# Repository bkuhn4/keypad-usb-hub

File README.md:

# keypad-usb-hub

## Getting started

To make it easy for you to get started with GitLab, here's a list of recommended next steps.

Already a pro? Just edit this README.md and make it your own. Want to make it easy? [Use the template at the bottom](#editing-this-readme)!

## Add your files

* \[ ] [Create](https://docs.gitlab.com/ee/user/project/repository/web_editor.html#create-a-file) or [upload](https://docs.gitlab.com/ee/user/project/repository/web_editor.html#upload-a-file) files
* \[ ] [Add files using the command line](https://docs.gitlab.com/ee/gitlab-basics/add-file.html#add-a-file-using-the-command-line) or push an existing Git repository with the following command:

```
cd existing\_repo
git remote add origin https://git.ece.iastate.edu/etg\_dev/micro\_sd\_card.git
git branch -M main
git push -uf origin main
```

## Integrate with your tools

* \[ ] [Set up project integrations](https://git.ece.iastate.edu/etg_dev/micro_sd_card/-/settings/integrations)

## Collaborate with your team

* \[ ] [Invite team members and collaborators](https://docs.gitlab.com/ee/user/project/members/)
* \[ ] [Create a new merge request](https://docs.gitlab.com/ee/user/project/merge_requests/creating_merge_requests.html)
* \[ ] [Automatically close issues from merge requests](https://docs.gitlab.com/ee/user/project/issues/managing_issues.html#closing-issues-automatically)
* \[ ] [Enable merge request approvals](https://docs.gitlab.com/ee/user/project/merge_requests/approvals/)
* \[ ] [Set auto-merge](https://docs.gitlab.com/ee/user/project/merge_requests/merge_when_pipeline_succeeds.html)

## Test and Deploy

Use the built-in continuous integration in GitLab.

* \[ ] [Get started with GitLab CI/CD](https://docs.gitlab.com/ee/ci/quick_start/index.html)
* \[ ] [Analyze your code for known vulnerabilities with Static Application Security Testing (SAST)](https://docs.gitlab.com/ee/user/application_security/sast/)
* \[ ] [Deploy to Kubernetes, Amazon EC2, or Amazon ECS using Auto Deploy](https://docs.gitlab.com/ee/topics/autodevops/requirements.html)
* \[ ] [Use pull-based deployments for improved Kubernetes management](https://docs.gitlab.com/ee/user/clusters/agent/)
* \[ ] [Set up protected environments](https://docs.gitlab.com/ee/ci/environments/protected_environments.html)

---

# Editing this README

When you're ready to make this README your own, just edit this file and use the handy template below (or feel free to structure it however you want - this is just a starting point!). Thanks to [makeareadme.com](https://www.makeareadme.com/) for this template.

## Suggestions for a good README

Every project is different, so consider which of these sections apply to yours. The sections used in the template are suggestions for most open source projects. Also keep in mind that while a README can be too long and detailed, too long is better than too short. If you think your README is too long, consider utilizing another form of documentation rather than cutting out information.

## Name

Choose a self-explaining name for your project.

## Description

Let people know what your project can do specifically. Provide context and add a link to any reference visitors might be unfamiliar with. A list of Features or a Background subsection can also be added here. If there are alternatives to your project, this is a good place to list differentiating factors.

## Badges

On some READMEs, you may see small images that convey metadata, such as whether or not all the tests are passing for the project. You can use Shields to add some to your README. Many services also have instructions for adding a badge.

## Visuals

Depending on what you are making, it can be a good idea to include screenshots or even a video (you'll frequently see GIFs rather than actual videos). Tools like ttygif can help, but check out Asciinema for a more sophisticated method.

## Installation

Within a particular ecosystem, there may be a common way of installing things, such as using Yarn, NuGet, or Homebrew. However, consider the possibility that whoever is reading your README is a novice and would like more guidance. Listing specific steps helps remove ambiguity and gets people to using your project as quickly as possible. If it only runs in a specific context like a particular programming language version or operating system or has dependencies that have to be installed manually, also add a Requirements subsection.

## Usage

Use examples liberally, and show the expected output if you can. It's helpful to have inline the smallest example of usage that you can demonstrate, while providing links to more sophisticated examples if they are too long to reasonably include in the README.

## Support

Tell people where they can go to for help. It can be any combination of an issue tracker, a chat room, an email address, etc.

## Roadmap

If you have ideas for releases in the future, it is a good idea to list them in the README.

## Contributing

State if you are open to contributions and what your requirements are for accepting them.

For people who want to make changes to your project, it's helpful to have some documentation on how to get started. Perhaps there is a script that they should run or some environment variables that they need to set. Make these steps explicit. These instructions could also be useful to your future self.

You can also document commands to lint the code or run tests. These steps help to ensure high code quality and reduce the likelihood that the changes inadvertently break something. Having instructions for running tests is especially helpful if it requires external setup, such as starting a Selenium server for testing in a browser.

## Authors and acknowledgment

Show your appreciation to those who have contributed to the project.

## License

For open source projects, say how it is licensed.

## Project status

If you have run out of energy or time for your project, put a note at the top of the README saying that development has slowed down or stopped completely. Someone may choose to fork your project or volunteer to step in as a maintainer or owner, allowing your project to keep going. You can also make an explicit request for maintainers.

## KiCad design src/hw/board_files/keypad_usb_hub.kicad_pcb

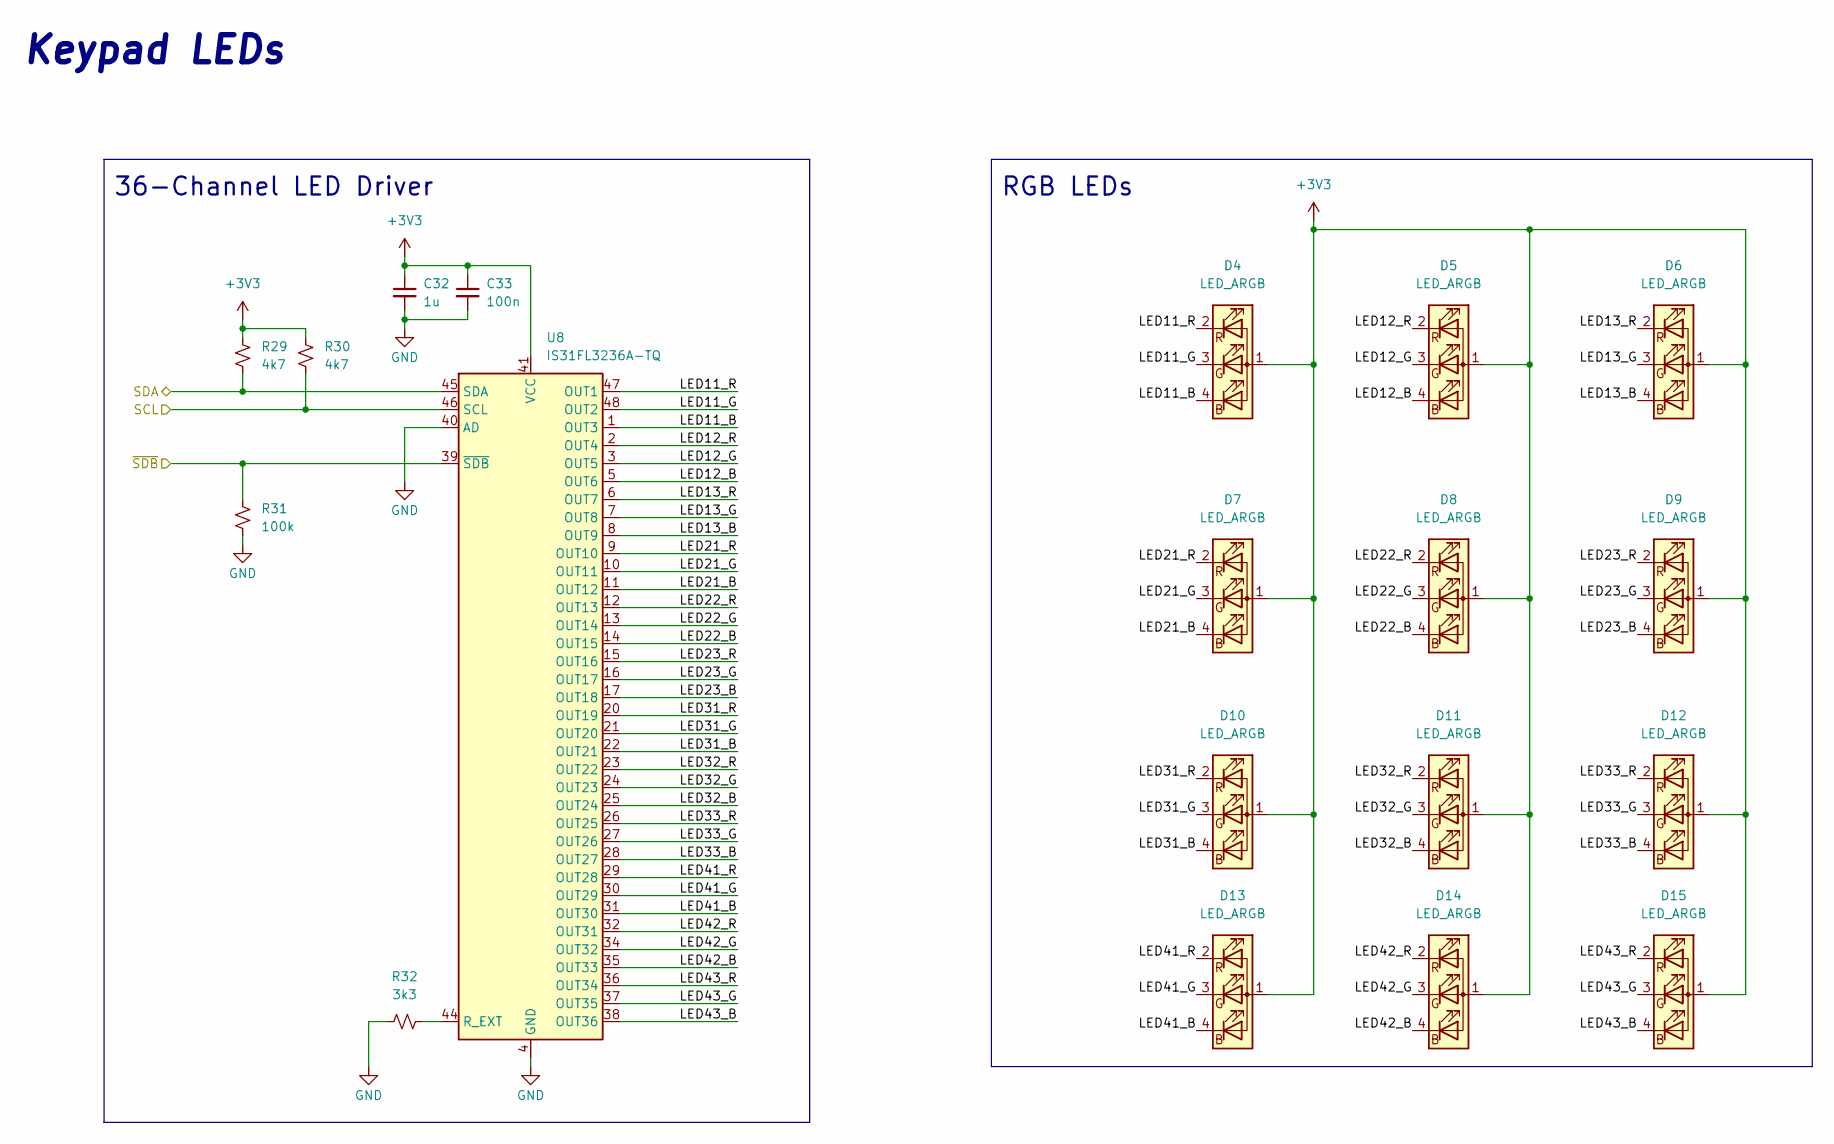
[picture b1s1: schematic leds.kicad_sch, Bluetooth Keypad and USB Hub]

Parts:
C32: 1u; C_0603_1608Metric_Pad1.08x0.95mm_HandSolder
C33: 100n; C_0603_1608Metric_Pad1.08x0.95mm_HandSolder
D4, D5, D6, D7, D8, D9, D10, D11, D12, D13, D14, D15: LED_ARGB; RGB_LED_6028_Reverse_Mount
R29, R30: 4k7; R_0603_1608Metric_Pad0.98x0.95mm_HandSolder
R31: 100k; R_0805_2012Metric_Pad1.20x1.40mm_HandSolder
R32: 3k3; R_0603_1608Metric_Pad0.98x0.95mm_HandSolder
U8: IS31FL3236A-TQ; TQFP-48-1EP_7x7mm_P0.5mm_EP4.11x4.11mm

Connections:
+3V3: C32.1, C33.1, D4.1 (A), D5.1 (A), D6.1 (A), D7.1 (A), D8.1 (A), D9.1 (A), D10.1 (A), D11.1 (A), D12.1 (A), D13.1 (A), D14.1 (A), D15.1 (A), R29.1, R30.1, U8.41 (VCC); also elsewhere on the board
/LEDs/LED11_B: D4.4 (BK), U8.1 (OUT3)
/LEDs/LED11_G: D4.3 (GK), U8.48 (OUT2)
/LEDs/LED11_R: D4.2 (RK), U8.47 (OUT1)
/LEDs/LED12_B: D5.4 (BK), U8.5 (OUT6)
/LEDs/LED12_G: D5.3 (GK), U8.3 (OUT5)
/LEDs/LED12_R: D5.2 (RK), U8.2 (OUT4)
/LEDs/LED13_B: D6.4 (BK), U8.8 (OUT9)
/LEDs/LED13_G: D6.3 (GK), U8.7 (OUT8)
/LEDs/LED13_R: D6.2 (RK), U8.6 (OUT7)
/LEDs/LED21_B: D7.4 (BK), U8.11 (OUT12)
/LEDs/LED21_G: D7.3 (GK), U8.10 (OUT11)
/LEDs/LED21_R: D7.2 (RK), U8.9 (OUT10)
/LEDs/LED22_B: D8.4 (BK), U8.14 (OUT15)
/LEDs/LED22_G: D8.3 (GK), U8.13 (OUT14)
/LEDs/LED22_R: D8.2 (RK), U8.12 (OUT13)
/LEDs/LED23_B: D9.4 (BK), U8.17 (OUT18)
/LEDs/LED23_G: D9.3 (GK), U8.16 (OUT17)
/LEDs/LED23_R: D9.2 (RK), U8.15 (OUT16)
/LEDs/LED31_B: D10.4 (BK), U8.22 (OUT21)
/LEDs/LED31_G: D10.3 (GK), U8.21 (OUT20)
/LEDs/LED31_R: D10.2 (RK), U8.20 (OUT19)
/LEDs/LED32_B: D11.4 (BK), U8.25 (OUT24)
/LEDs/LED32_G: D11.3 (GK), U8.24 (OUT23)
/LEDs/LED32_R: D11.2 (RK), U8.23 (OUT22)
/LEDs/LED33_B: D12.4 (BK), U8.28 (OUT27)
/LEDs/LED33_G: D12.3 (GK), U8.27 (OUT26)
/LEDs/LED33_R: D12.2 (RK), U8.26 (OUT25)
/LEDs/LED41_B: D13.4 (BK), U8.31 (OUT30)
/LEDs/LED41_G: D13.3 (GK), U8.30 (OUT29)
/LEDs/LED41_R: D13.2 (RK), U8.29 (OUT28)
/LEDs/LED42_B: D14.4 (BK), U8.35 (OUT33)
/LEDs/LED42_G: D14.3 (GK), U8.34 (OUT32)
/LEDs/LED42_R: D14.2 (RK), U8.32 (OUT31)
/LEDs/LED43_B: D15.4 (BK), U8.38 (OUT36)
/LEDs/LED43_G: D15.3 (GK), U8.37 (OUT35)
/LEDs/LED43_R: D15.2 (RK), U8.36 (OUT34)
/LEDs/SCL: R30.2, U8.46 (SCL); also elsewhere on the board
/LEDs/SDA: R29.2, U8.45 (SDA); also elsewhere on the board
/LEDs/~SDB: R31.1, U8.39 (~SDB); also elsewhere on the board
GND: C32.2, C33.2, R31.2, R32.2, U8.4 (GND), U8.18 (GND), U8.19 (GND), U8.33 (GND), U8.40 (AD), U8.42 (GND), U8.43 (GND), U8.49 (GND); also elsewhere on the board
unnamed: R32.1, U8.44 (R_EXT)

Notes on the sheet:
Keypad LEDs
RGB LEDs
36-Channel LED Driver

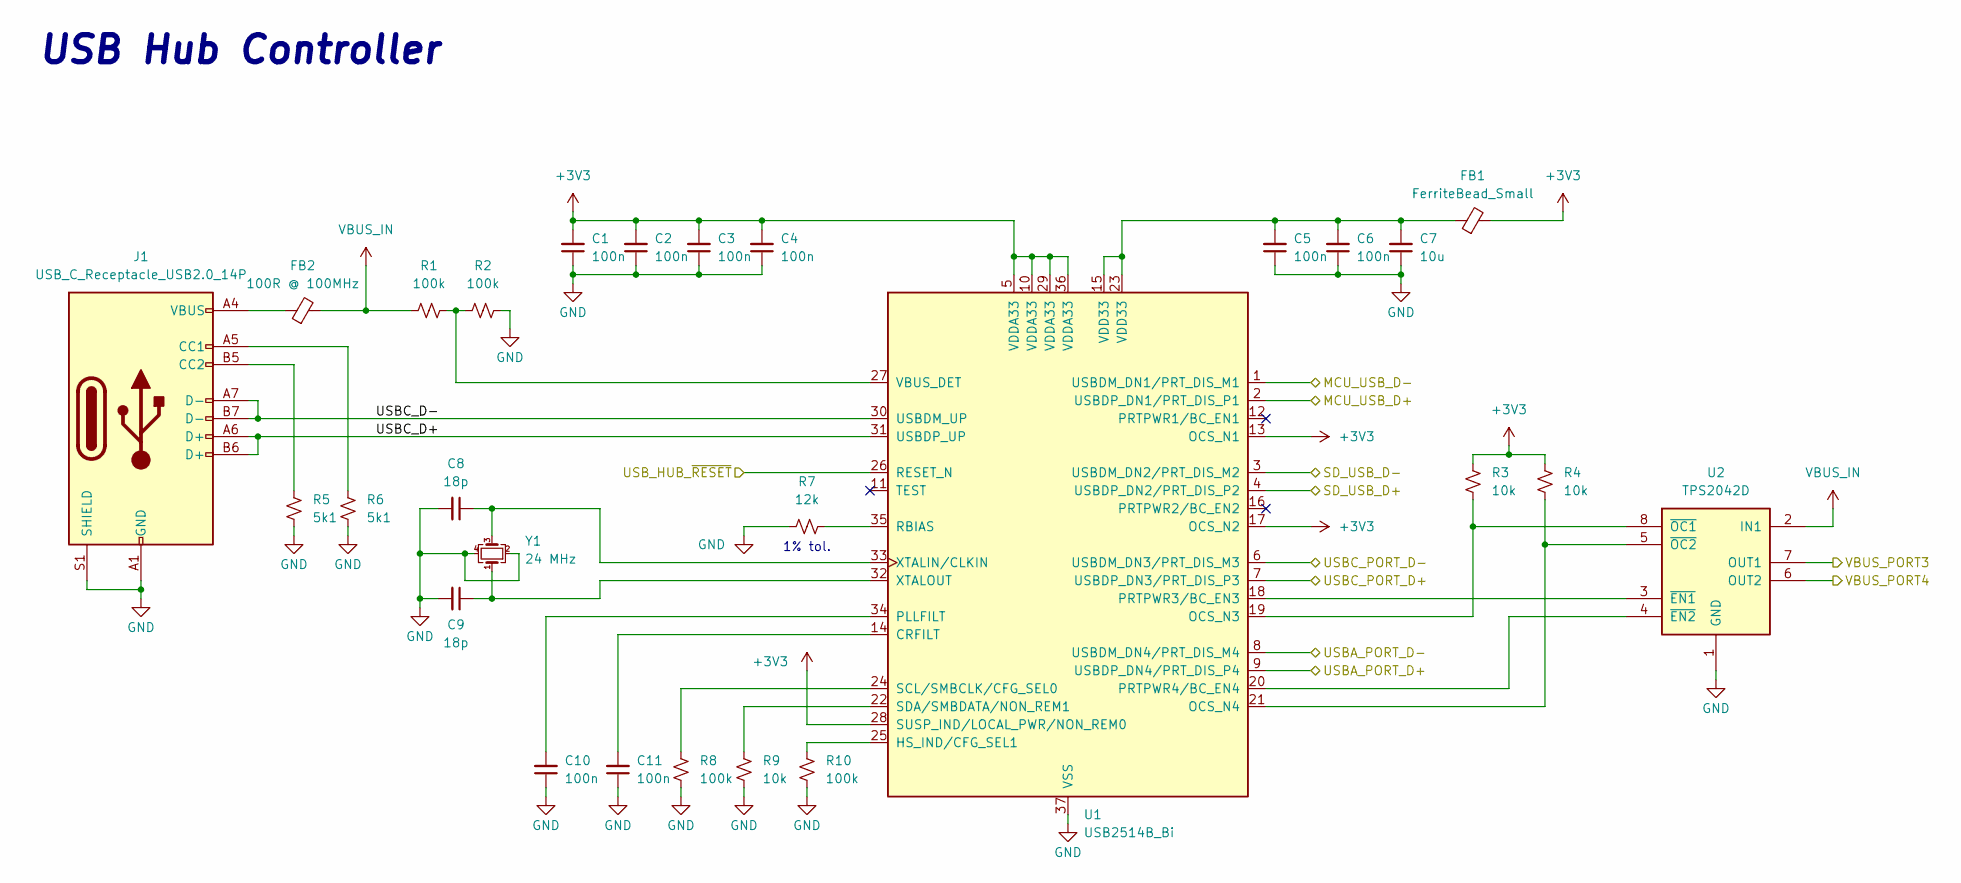
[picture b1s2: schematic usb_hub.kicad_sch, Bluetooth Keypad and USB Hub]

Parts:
C1, C2, C3, C4, C5, C6, C10, C11: 100n; C_0603_1608Metric_Pad1.08x0.95mm_HandSolder
C7: 10u; C_0805_2012Metric_Pad1.18x1.45mm_HandSolder
C8, C9: 18p; C_0603_1608Metric_Pad1.08x0.95mm_HandSolder
FB1: FerriteBead_Small; L_0603_1608Metric_Pad1.05x0.95mm_HandSolder
FB2: 100R @ 100MHz; L_0805_2012Metric_Pad1.15x1.40mm_HandSolder
J1: USB_C_Receptacle_USB2.0_14P; USB_C_Receptacle_GCT_USB4105-xx-A_16P_TopMnt_Horizontal
R1, R2, R8, R10: 100k; R_0805_2012Metric_Pad1.20x1.40mm_HandSolder
R3, R4, R9: 10k; R_0603_1608Metric_Pad0.98x0.95mm_HandSolder
R5, R6: 5k1; R_0603_1608Metric_Pad0.98x0.95mm_HandSolder
R7: 12k; R_0603_1608Metric_Pad0.98x0.95mm_HandSolder
U1: USB2514B_Bi; QFN-36-1EP_6x6mm_P0.5mm_EP3.7x3.7mm
U2: TPS2042D; SOIC-8_3.9x4.9mm_P1.27mm
Y1: 24 MHz; Crystal_SMD_Abracon_ABM8G-4Pin_3.2x2.5mm

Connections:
+3V3: C1.2, C2.2, C3.2, C4.2, FB1.2, R3.2, R4.2, U1.5 (VDDA33), U1.10 (VDDA33), U1.13 (OCS_N1), U1.17 (OCS_N2), U1.28 (SUSP_IND/LOCAL_PWR/NON_REM0), U1.29 (VDDA33), U1.36 (VDDA33); also elsewhere on the board
/Microcontroller and Power/MCU_USB_D+: U1.2 (USBDP_DN1/PRT_DIS_P1); also elsewhere on the board
/Microcontroller and Power/MCU_USB_D-: U1.1 (USBDM_DN1/PRT_DIS_M1); also elsewhere on the board
/Microcontroller and Power/USB_HUB_~RESET: U1.26 (RESET_N); also elsewhere on the board
/Receptacles/SD_USB_D+: U1.4 (USBDP_DN2/PRT_DIS_P2); also elsewhere on the board
/Receptacles/SD_USB_D-: U1.3 (USBDM_DN2/PRT_DIS_M2); also elsewhere on the board
/Receptacles/USBA_PORT_D+: U1.9 (USBDP_DN4/PRT_DIS_P4); also elsewhere on the board
/Receptacles/USBA_PORT_D-: U1.8 (USBDM_DN4/PRT_DIS_M4); also elsewhere on the board
/Receptacles/USBC_PORT_D+: U1.7 (USBDP_DN3/PRT_DIS_P3); also elsewhere on the board
/Receptacles/USBC_PORT_D-: U1.6 (USBDM_DN3/PRT_DIS_M3); also elsewhere on the board
/Receptacles/VBUS_PORT4: U2.6 (OUT2); also elsewhere on the board
/USB Hub Controller/USBC_D+: J1.A6 (D+), J1.B6 (D+), U1.31 (USBDP_UP)
/USB Hub Controller/USBC_D-: J1.A7 (D-), J1.B7 (D-), U1.30 (USBDM_UP)
GND: C1.1, C2.1, C3.1, C4.1, C5.1, C6.1, C7.1, C8.2, C9.2, C10.1, C11.1, J1.A1 (GND), J1.A12 (GND), J1.B1 (GND), J1.B12 (GND), J1.S1 (SHIELD), R2.1, R5.1, R6.1, R7.1, R8.1, R9.1, R10.1, U1.37 (VSS), U2.1 (GND), Y1.2, Y1.4; also elsewhere on the board
unnamed: C5.2, C6.2, C7.2, FB1.1, U1.15 (VDD33), U1.23 (VDD33)
unnamed: FB2.1, J1.A4 (VBUS), J1.A9 (VBUS), J1.B4 (VBUS), J1.B9 (VBUS)
unnamed: J1.A5 (CC1), R6.2
unnamed: J1.B5 (CC2), R5.2
unnamed: C11.2, U1.14 (CRFILT)
unnamed: R10.2, U1.25 (HS_IND/CFG_SEL1)
unnamed: R3.1, U1.19 (OCS_N3), U2.8 (~OC1)
unnamed: R4.1, U1.21 (OCS_N4), U2.5 (~OC2)
unnamed: C10.2, U1.34 (PLLFILT)
unnamed: U1.18 (PRTPWR3/BC_EN3), U2.3 (~EN1)
unnamed: U1.20 (PRTPWR4/BC_EN4), U2.4 (~EN2)
unnamed: R7.2, U1.35 (RBIAS)
unnamed: R8.2, U1.24 (SCL/SMBCLK/CFG_SEL0)
unnamed: R9.2, U1.22 (SDA/SMBDATA/NON_REM1)
unnamed: R1.1, R2.2, U1.27 (VBUS_DET)
unnamed: C8.1, U1.33 (XTALIN/CLKIN), Y1.3
unnamed: C9.1, U1.32 (XTALOUT), Y1.1
VBUS_IN: FB2.2, R1.2, U2.2 (IN1); also elsewhere on the board
VBUS_PORT3: U2.7 (OUT1); also elsewhere on the board

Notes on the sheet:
USB Hub Controller
1% tol.

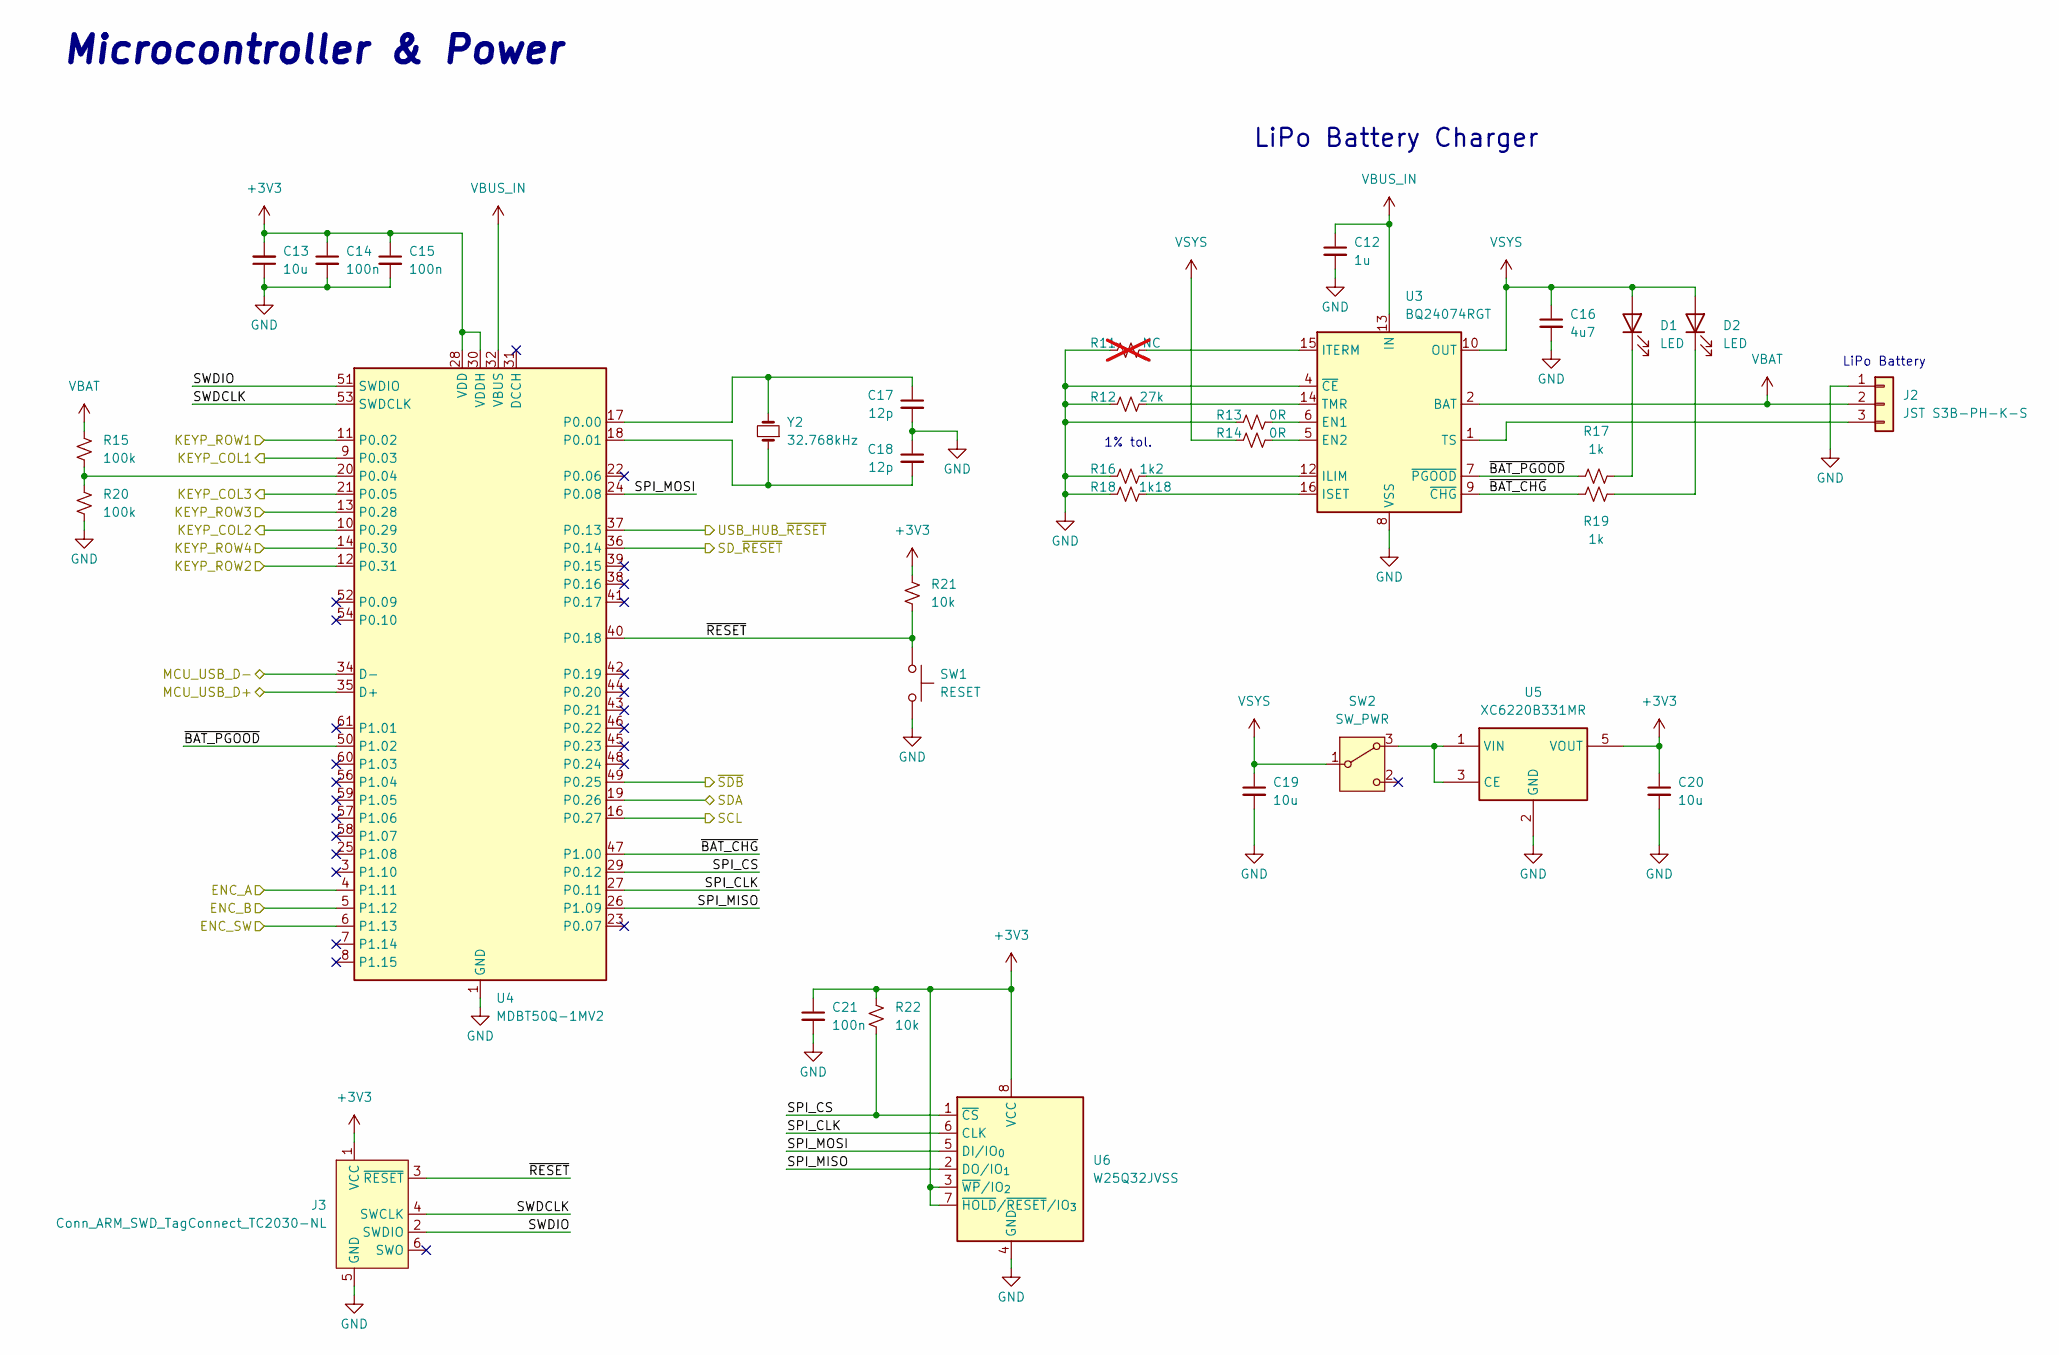
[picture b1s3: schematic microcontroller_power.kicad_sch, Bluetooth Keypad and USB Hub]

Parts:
C12: 1u; C_0603_1608Metric_Pad1.08x0.95mm_HandSolder
C13, C19, C20: 10u; C_0805_2012Metric_Pad1.18x1.45mm_HandSolder
C14, C15, C21: 100n; C_0603_1608Metric_Pad1.08x0.95mm_HandSolder
C16: 4u7; C_0805_2012Metric_Pad1.18x1.45mm_HandSolder
C17, C18: 12p; C_0603_1608Metric_Pad1.08x0.95mm_HandSolder
D1, D2: LED; LED_0603_1608Metric_Pad1.05x0.95mm_HandSolder
J2: JST S3B-PH-K-S; JST_PH_S3B-PH-K_1x03_P2.00mm_Horizontal
J3: Conn_ARM_SWD_TagConnect_TC2030-NL; Tag-Connect_TC2030-IDC-NL_2x03_P1.27mm_Vertical
R11: NC; R_0603_1608Metric_Pad0.98x0.95mm_HandSolder; not fitted
R12: 27k; R_0603_1608Metric_Pad0.98x0.95mm_HandSolder
R13, R14: 0R; R_0603_1608Metric_Pad0.98x0.95mm_HandSolder
R15, R20: 100k; R_0805_2012Metric_Pad1.20x1.40mm_HandSolder
R16: 1k2; R_0603_1608Metric_Pad0.98x0.95mm_HandSolder
R17, R19: 1k; R_0603_1608Metric_Pad0.98x0.95mm_HandSolder
R18: 1k18; R_0603_1608Metric_Pad0.98x0.95mm_HandSolder
R21, R22: 10k; R_0603_1608Metric_Pad0.98x0.95mm_HandSolder
SW1: RESET; SW_PUSH_6mm
SW2: SW_PWR; SW_Slide-03_Wuerth-WS-SLTV_10x2.5x6.4_P2.54mm
U3: BQ24074RGT; VQFN-16-1EP_3x3mm_P0.5mm_EP1.6x1.6mm
U4: MDBT50Q-1MV2; Raytac_MDBT50Q
U5: XC6220B331MR; SOT-23-5
U6: W25Q32JVSS; SOIC-8_5.3x5.3mm_P1.27mm
Y2: 32.768kHz; Crystal_SMD_3215-2Pin_3.2x1.5mm

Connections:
+3V3: C13.2, C14.1, C15.1, C20.1, C21.1, J3.1 (VCC), R21.2, R22.2, U4.28 (VDD), U4.30 (VDDH), U5.5 (VOUT), U6.3 (~WP/IO_{2}), U6.7 (~HOLD/~RESET/IO_{3}), U6.8 (VCC); also elsewhere on the board
/LEDs/SCL: U4.16 (P0.27); also elsewhere on the board
/LEDs/SDA: U4.19 (P0.26); also elsewhere on the board
/LEDs/~SDB: U4.49 (P0.25); also elsewhere on the board
/Microcontroller and Power/ENC_A: U4.4 (P1.11); also elsewhere on the board
/Microcontroller and Power/ENC_B: U4.5 (P1.12); also elsewhere on the board
/Microcontroller and Power/ENC_SW: U4.6 (P1.13); also elsewhere on the board
/Microcontroller and Power/KEYP_COL1: U4.9 (P0.03); also elsewhere on the board
/Microcontroller and Power/KEYP_COL2: U4.10 (P0.29); also elsewhere on the board
/Microcontroller and Power/KEYP_COL3: U4.21 (P0.05); also elsewhere on the board
/Microcontroller and Power/KEYP_ROW1: U4.11 (P0.02); also elsewhere on the board
/Microcontroller and Power/KEYP_ROW2: U4.12 (P0.31); also elsewhere on the board
/Microcontroller and Power/KEYP_ROW3: U4.13 (P0.28); also elsewhere on the board
/Microcontroller and Power/KEYP_ROW4: U4.14 (P0.30); also elsewhere on the board
/Microcontroller and Power/MCU_USB_D+: U4.35 (D+); also elsewhere on the board
/Microcontroller and Power/MCU_USB_D-: U4.34 (D-); also elsewhere on the board
/Microcontroller and Power/SD_~RESET: U4.36 (P0.14); also elsewhere on the board
/Microcontroller and Power/SPI_CLK: U4.27 (P0.11), U6.6 (CLK)
/Microcontroller and Power/SPI_CS: R22.1, U4.29 (P0.12), U6.1 (~CS)
/Microcontroller and Power/SPI_MISO: U4.26 (P1.09), U6.2 (DO/IO_{1})
/Microcontroller and Power/SPI_MOSI: U4.24 (P0.08), U6.5 (DI/IO_{0})
/Microcontroller and Power/SWDCLK: J3.4 (SWCLK), U4.53 (SWDCLK)
/Microcontroller and Power/SWDIO: J3.2 (SWDIO), U4.51 (SWDIO)
/Microcontroller and Power/USB_HUB_~RESET: U4.37 (P0.13); also elsewhere on the board
/Microcontroller and Power/~BAT_CHG: R19.1, U3.9 (~CHG), U4.47 (P1.00)
/Microcontroller and Power/~BAT_PGOOD: R17.1, U3.7 (~PGOOD), U4.50 (P1.02)
/Microcontroller and Power/~RESET: J3.3 (~RESET), R21.1, SW1.1, U4.40 (P0.18)
GND: C12.2, C13.1, C14.2, C15.2, C16.2, C17.2, C18.1, C19.2, C20.2, C21.2, J2.1, J3.5 (GND), R11.2, R12.2, R13.2, R16.2, R18.2, R20.2, SW1.2, U3.4 (~CE), U3.8 (VSS), U3.17 (VSS), U4.1 (GND), U4.2 (GND), U4.15 (GND), U4.33 (GND), U4.55 (GND), U5.2 (GND), U6.4 (GND); also elsewhere on the board
unnamed: D1.1 (K), R17.2
unnamed: D2.1 (K), R19.2
unnamed: J2.3, U3.1 (TS)
unnamed: SW2.3 (A), U5.1 (VIN), U5.3 (CE)
unnamed: R13.1, U3.6 (EN1)
unnamed: R14.1, U3.5 (EN2)
unnamed: R16.1, U3.12 (ILIM)
unnamed: R18.1, U3.16 (ISET)
unnamed: R11.1, U3.15 (ITERM)
unnamed: R12.1, U3.14 (TMR)
unnamed: C17.1, U4.17 (P0.00), Y2.2
unnamed: C18.2, U4.18 (P0.01), Y2.1
unnamed: R15.2, R20.1, U4.20 (P0.04)
VBAT: J2.2, R15.1, U3.2 (BAT), U3.3 (BAT)
VBUS_IN: C12.1, U3.13 (IN), U4.32 (VBUS); also elsewhere on the board
VSYS: C16.1, C19.1, D1.2 (A), D2.2 (A), R14.2, SW2.1 (B), U3.10 (OUT), U3.11 (OUT)

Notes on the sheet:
LiPo Battery
1% tol.
Microcontroller & Power
LiPo Battery Charger

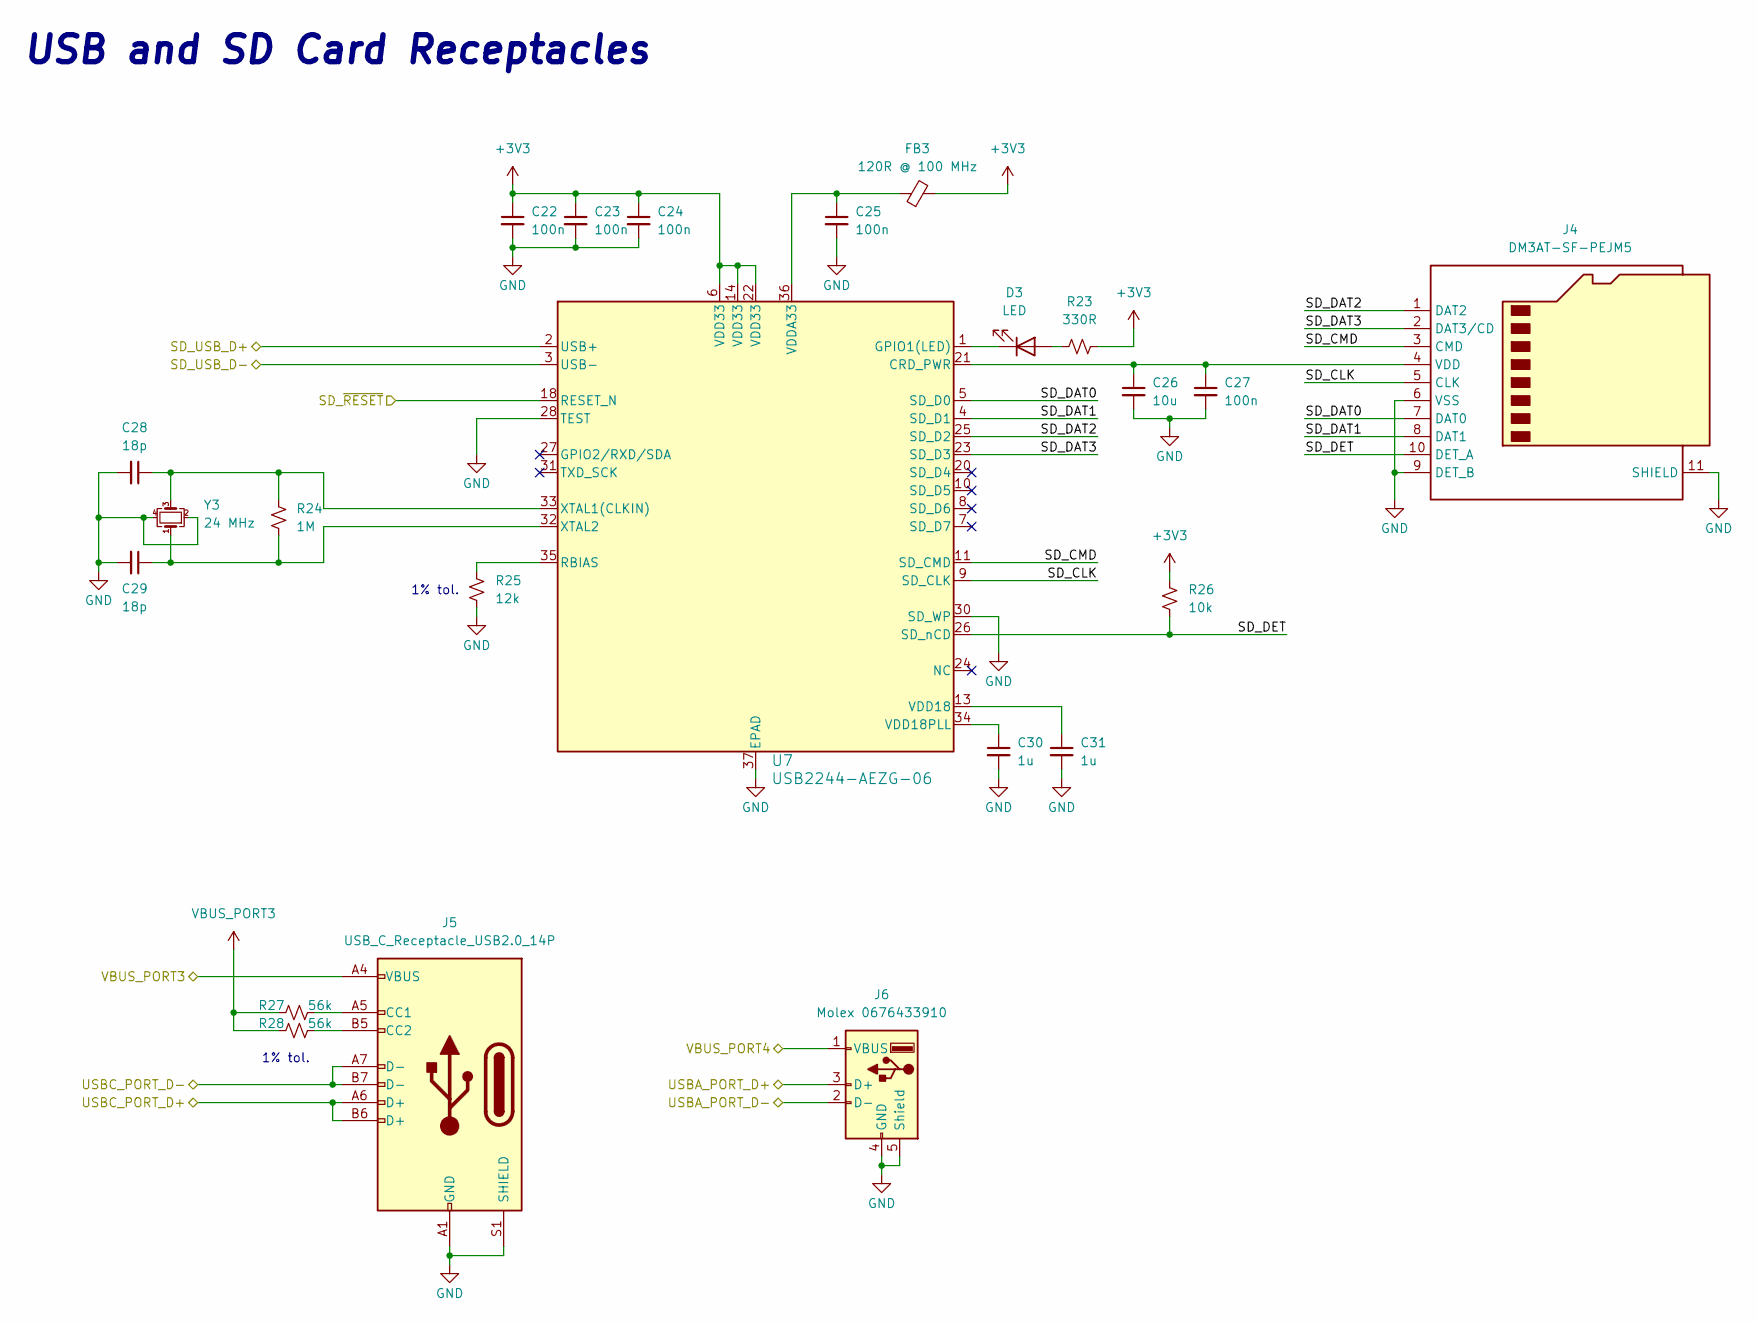
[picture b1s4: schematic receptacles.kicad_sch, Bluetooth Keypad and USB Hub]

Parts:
C22, C23, C24, C25, C27: 100n; C_0603_1608Metric_Pad1.08x0.95mm_HandSolder
C26: 10u; C_0805_2012Metric_Pad1.18x1.45mm_HandSolder
C28, C29: 18p; C_0603_1608Metric_Pad1.08x0.95mm_HandSolder
C30, C31: 1u; C_0603_1608Metric_Pad1.08x0.95mm_HandSolder
D3: LED; LED_0603_1608Metric_Pad1.05x0.95mm_HandSolder
FB3: 120R @ 100 MHz; L_0603_1608Metric_Pad1.05x0.95mm_HandSolder
J4: DM3AT-SF-PEJM5; microSD_HC_Hirose_DM3AT-SF-PEJM5
J5: USB_C_Receptacle_USB2.0_14P; USB_C_Receptacle_GCT_USB4105-xx-A_16P_TopMnt_Horizontal
J6: Molex 0676433910; USB_A_Molex_67643_Horizontal
R23: 330R; R_0603_1608Metric_Pad0.98x0.95mm_HandSolder
R24: 1M; R_0805_2012Metric_Pad1.20x1.40mm_HandSolder
R25: 12k; R_0603_1608Metric_Pad0.98x0.95mm_HandSolder
R26: 10k; R_0603_1608Metric_Pad0.98x0.95mm_HandSolder
R27, R28: 56k; R_0603_1608Metric_Pad0.98x0.95mm_HandSolder
U7: USB2244-AEZG-06; QFN-36-1EP_6x6mm_P0.5mm_EP4.1x4.1mm_ThermalVias
Y3: 24 MHz; Crystal_SMD_Abracon_ABM8G-4Pin_3.2x2.5mm

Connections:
+3V3: C22.1, C23.1, C24.1, FB3.2, R23.2, R26.2, U7.6 (VDD33), U7.14 (VDD33), U7.22 (VDD33); also elsewhere on the board
/Microcontroller and Power/SD_~RESET: U7.18 (RESET_N); also elsewhere on the board
/Receptacles/SD_CLK: J4.5 (CLK), U7.9 (SD_CLK)
/Receptacles/SD_CMD: J4.3 (CMD), U7.11 (SD_CMD)
/Receptacles/SD_DAT0: J4.7 (DAT0), U7.5 (SD_D0)
/Receptacles/SD_DAT1: J4.8 (DAT1), U7.4 (SD_D1)
/Receptacles/SD_DAT2: J4.1 (DAT2), U7.25 (SD_D2)
/Receptacles/SD_DAT3: J4.2 (DAT3/CD), U7.23 (SD_D3)
/Receptacles/SD_DET: J4.10 (DET_A), R26.1, U7.26 (SD_nCD)
/Receptacles/SD_USB_D+: U7.2 (USB+); also elsewhere on the board
/Receptacles/SD_USB_D-: U7.3 (USB-); also elsewhere on the board
/Receptacles/USBA_PORT_D+: J6.3 (D+); also elsewhere on the board
/Receptacles/USBA_PORT_D-: J6.2 (D-); also elsewhere on the board
/Receptacles/USBC_PORT_D+: J5.A6 (D+), J5.B6 (D+); also elsewhere on the board
/Receptacles/USBC_PORT_D-: J5.A7 (D-), J5.B7 (D-); also elsewhere on the board
/Receptacles/VBUS_PORT4: J6.1 (VBUS); also elsewhere on the board
GND: C22.2, C23.2, C24.2, C25.2, C26.2, C27.2, C28.2, C29.2, C30.2, C31.2, J4.6 (VSS), J4.9 (DET_B), J4.11 (SHIELD), J5.A1 (GND), J5.A12 (GND), J5.B1 (GND), J5.B12 (GND), J5.S1 (SHIELD), J6.4 (GND), J6.5 (Shield), R25.2, U7.28 (TEST), U7.30 (SD_WP), U7.37 (EPAD), Y3.2, Y3.4; also elsewhere on the board
unnamed: D3.2 (A), R23.1
unnamed: D3.1 (K), U7.1 (GPIO1(LED))
unnamed: C26.1, C27.1, J4.4 (VDD), U7.21 (CRD_PWR)
unnamed: J5.A5 (CC1), R27.1
unnamed: J5.B5 (CC2), R28.1
unnamed: R25.1, U7.35 (RBIAS)
unnamed: C31.1, U7.13 (VDD18)
unnamed: C30.1, U7.34 (VDD18PLL)
unnamed: C25.1, FB3.1, U7.36 (VDDA33)
unnamed: C28.1, R24.1, U7.33 (XTAL1(CLKIN)), Y3.3
unnamed: C29.1, R24.2, U7.32 (XTAL2), Y3.1
VBUS_PORT3: J5.A4 (VBUS), J5.A9 (VBUS), J5.B4 (VBUS), J5.B9 (VBUS), R27.2, R28.2; also elsewhere on the board

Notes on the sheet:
1% tol.
USB and SD Card Receptacles

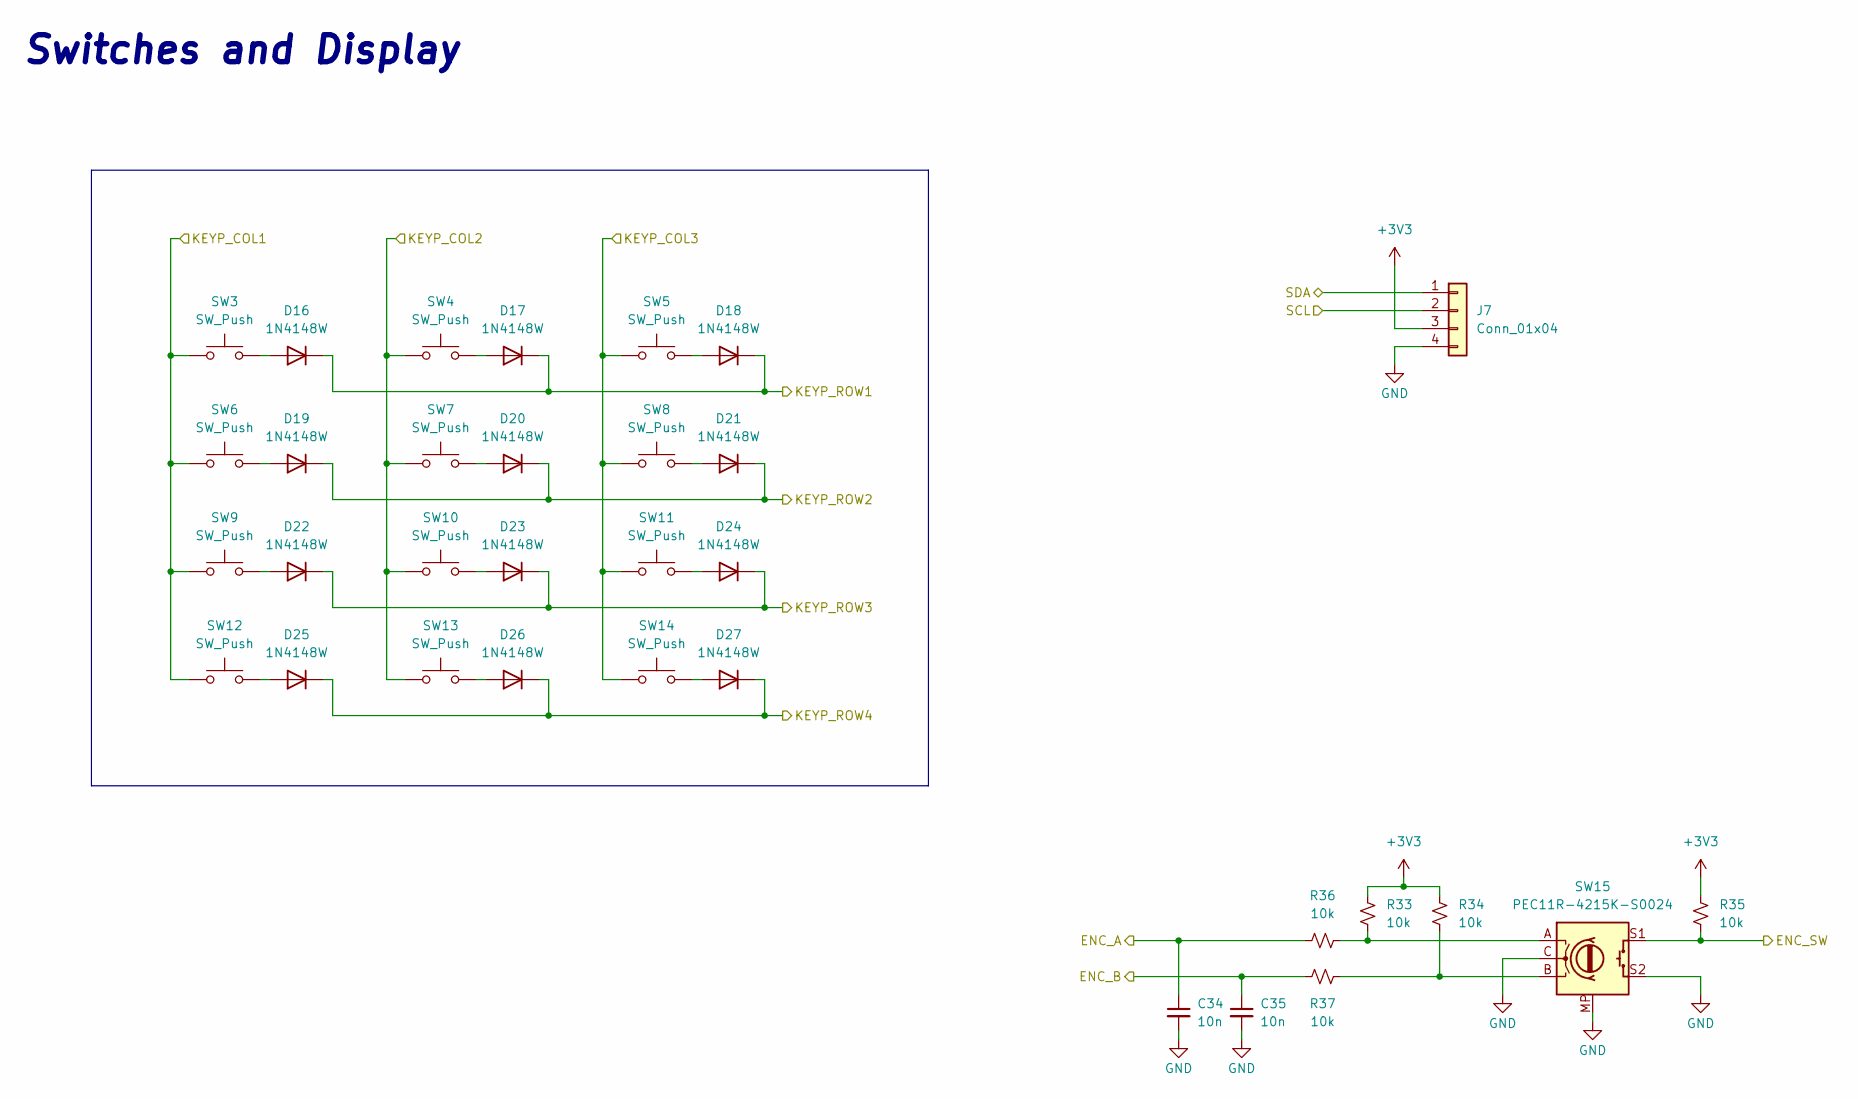
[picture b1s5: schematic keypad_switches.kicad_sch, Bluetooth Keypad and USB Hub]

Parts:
C34, C35: 10n; C_0603_1608Metric_Pad1.08x0.95mm_HandSolder
D16, D17, D18, D19, D20, D21, D22, D23, D24, D25, D26, D27: 1N4148W; D_SOD-123
J7: Conn_01x04; PinSocket_1x04_P2.54mm_Vertical
R33, R34, R35, R36, R37: 10k; R_0603_1608Metric_Pad0.98x0.95mm_HandSolder
SW3, SW4, SW5, SW6, SW7, SW8, SW9, SW10, SW11, SW12, SW13, SW14: SW_Push; SW_Cherry_MX_1.00u_PCB
SW15: PEC11R-4215K-S0024; RotaryEncoder_Alps_EC12E-Switch_Vertical_H20mm

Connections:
+3V3: J7.3, R33.1, R34.1, R35.1; also elsewhere on the board
/LEDs/SCL: J7.2; also elsewhere on the board
/LEDs/SDA: J7.1; also elsewhere on the board
/Microcontroller and Power/ENC_A: C34.1, R36.1; also elsewhere on the board
/Microcontroller and Power/ENC_B: C35.1, R37.1; also elsewhere on the board
/Microcontroller and Power/ENC_SW: R35.2, SW15.S1; also elsewhere on the board
/Microcontroller and Power/KEYP_COL1: SW3.1, SW6.1, SW9.1, SW12.1; also elsewhere on the board
/Microcontroller and Power/KEYP_COL2: SW4.1, SW7.1, SW10.1, SW13.1; also elsewhere on the board
/Microcontroller and Power/KEYP_COL3: SW5.1, SW8.1, SW11.1, SW14.1; also elsewhere on the board
/Microcontroller and Power/KEYP_ROW1: D16.1 (K), D17.1 (K), D18.1 (K); also elsewhere on the board
/Microcontroller and Power/KEYP_ROW2: D22.1 (K), D23.1 (K), D24.1 (K); also elsewhere on the board
/Microcontroller and Power/KEYP_ROW3: D19.1 (K), D20.1 (K), D21.1 (K); also elsewhere on the board
/Microcontroller and Power/KEYP_ROW4: D25.1 (K), D26.1 (K), D27.1 (K); also elsewhere on the board
GND: C34.2, C35.2, J7.4, SW15.C, SW15.MP, SW15.S2; also elsewhere on the board
unnamed: D16.2 (A), SW3.2
unnamed: D17.2 (A), SW4.2
unnamed: D18.2 (A), SW5.2
unnamed: D19.2 (A), SW6.2
unnamed: D20.2 (A), SW7.2
unnamed: D21.2 (A), SW8.2
unnamed: D22.2 (A), SW9.2
unnamed: D23.2 (A), SW10.2
unnamed: D24.2 (A), SW11.2
unnamed: D25.2 (A), SW12.2
unnamed: D26.2 (A), SW13.2
unnamed: D27.2 (A), SW14.2
unnamed: R33.2, R36.2, SW15.A
unnamed: R34.2, R37.2, SW15.B

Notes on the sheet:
Switches and Display

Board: 2 copper layers, 135 parts (15 on the bottom side), 140 nets, no tracks yet.

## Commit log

2025-12-14 Changed some ICs
2025-12-14 Added datasheets
2025-12-14 Started SD card bridge symbol
2025-12-17 Made USB hub symbol
2025-12-18 Schematic progress
2025-12-21 Finishing schematic. Need to review and clean up
2026-01-10 Added power switch
2026-01-11 Added all footprints, need to connect switches to MCU
2026-01-25 Added rotary encoder and OLED. Started laying out board then I need to review schematic and change pinout if needed
2026-01-26 Working on layout
